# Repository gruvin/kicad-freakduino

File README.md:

# kicad-freakduino
## KiCADifying the Freakduino

I have longed for years to be able to make my own 2.4GHz, digital wireless radios.  Then I discovered and purchased a 
couple of <a href='http://www.freaklabsstore.com/index.php?main_page=product_info&cPath=22&products_id=204&zenid=f07iqog0jf6pku1qjimmd3q934'>FreakLabs "Freakduino v2.1a" boards</a>, 
as a means to learn more about low level, digital 2.4GHz RF communications. With my desire for learning, 
combined with my preference for open source EDA tools, this project was born.

<blockquote><i>Image right: Latest (final?) KiCAD-Freakduino prototype, version 1.2, revision r189</i></blockquote>

<blockquote><i>Building the three prototypes to get to this stage cost me enough to buy about ten original Freakduinos. 
Even to build one of my final version 1.2 boards, by hand and using retail priced parts, it costs significantly more 
than an original Freakduino. So if you just want to get up and running painlessly with a working board, I recommend 
you  simply <a href='http://www.freaklabsstore.com/index.php?main_page=product_info&cPath=22&products_id=204&zenid=f07iqog0jf6pku1qjimmd3q934'>buy the real thing</a>.</i></blockquote>

These Arduino compatible boards use an Atmel radio chip, intended for Zigbee standard communications. Akiba (of Freaklabs) 
wrote, "Chibi" (Japanese for "Midget") -- a light-weight communications stack, which works very well and makes 
understanding how things fit together in these systems very much simpler than a full ZigBee stack. Certainly, 
Chibi more than suffices for anything I can imagine needing for my own projects. The Arduino targeted version 
has its own project site named, <a href='http://www.freaklabs.org/index.php/chibiArduino.html'>chibiArduino</a>.

Eventually, I want to make my own boards, based on what I've learned here -- not Arduino boards, just MCU+RF 
chip and thus much smaller. In the meantime, since I had only theoretical experience with 2.4GHz radio 
communications, making my own version of a Freakduino board seemed like a good place to start. "Standing on 
the shoulders of giants", sort of thing. ;-)

I use only open source EDA tools (mostly KiCAD) for schematic capture and PCB layout design of my open source 
projects. This meant re-designing a schematic and board layout from scratch, based on the open materials 
published by FreakLabs, to whom we are all obviously very thankful. In the end, I also made a few minor 
changes to the design -- mostly due to different parts availability in my part of the world. But I've kept 
the overall layout very similar, so that the original Freakduino user-level documentation still applies 
-- jumper locations, switch settings, etc. For example, my version has a different 5-to-3.3 Volt  level 
shifter chip. The battery boost-regulator circuit is also different and is implemented in surface mount 
parts as a standard feature of the board.

The original Freakduino is already publicly licensed (Creative Commons Attribution-ShareAlike v3.0). But I 
wanted to let Akiba know what I was doing and to thank him personally for his work. I received his blessing 
2013-07-16 and immediately created this Google Code project. Thanks Akiba. I am sure we all really appreciate 
your efforts!

<h2>Progress as at 2013-11-07</h2>

My KiCAD design has now gone through several revisions and improvements. There are some changes to the 
components used, due to local availability as much as anything. But I've kept all the switches and jumper 
locations and functions the same as the original, such that the existing Freakduino v2.1a user documentation 
still applies.

I had revision <a href='https://code.google.com/p/kicad-freakduino/source/detail?r=101'>r101</a> PCBs 
fabricated. But there were errors found before those even arrived. Revision r116 was then fabricated 
and subsequently built. Unfortunately, that had errors as well and needed patching to get working. See 
<a href='Milestones.md'>Milestones</a> for details.

Finally, a version 1.2 revision r189 was built and seems to have come out all OK. Yay \o/

Below is a KiCAD 3D view of the present, r181 design, which is almost identical to the final 
r189 ...

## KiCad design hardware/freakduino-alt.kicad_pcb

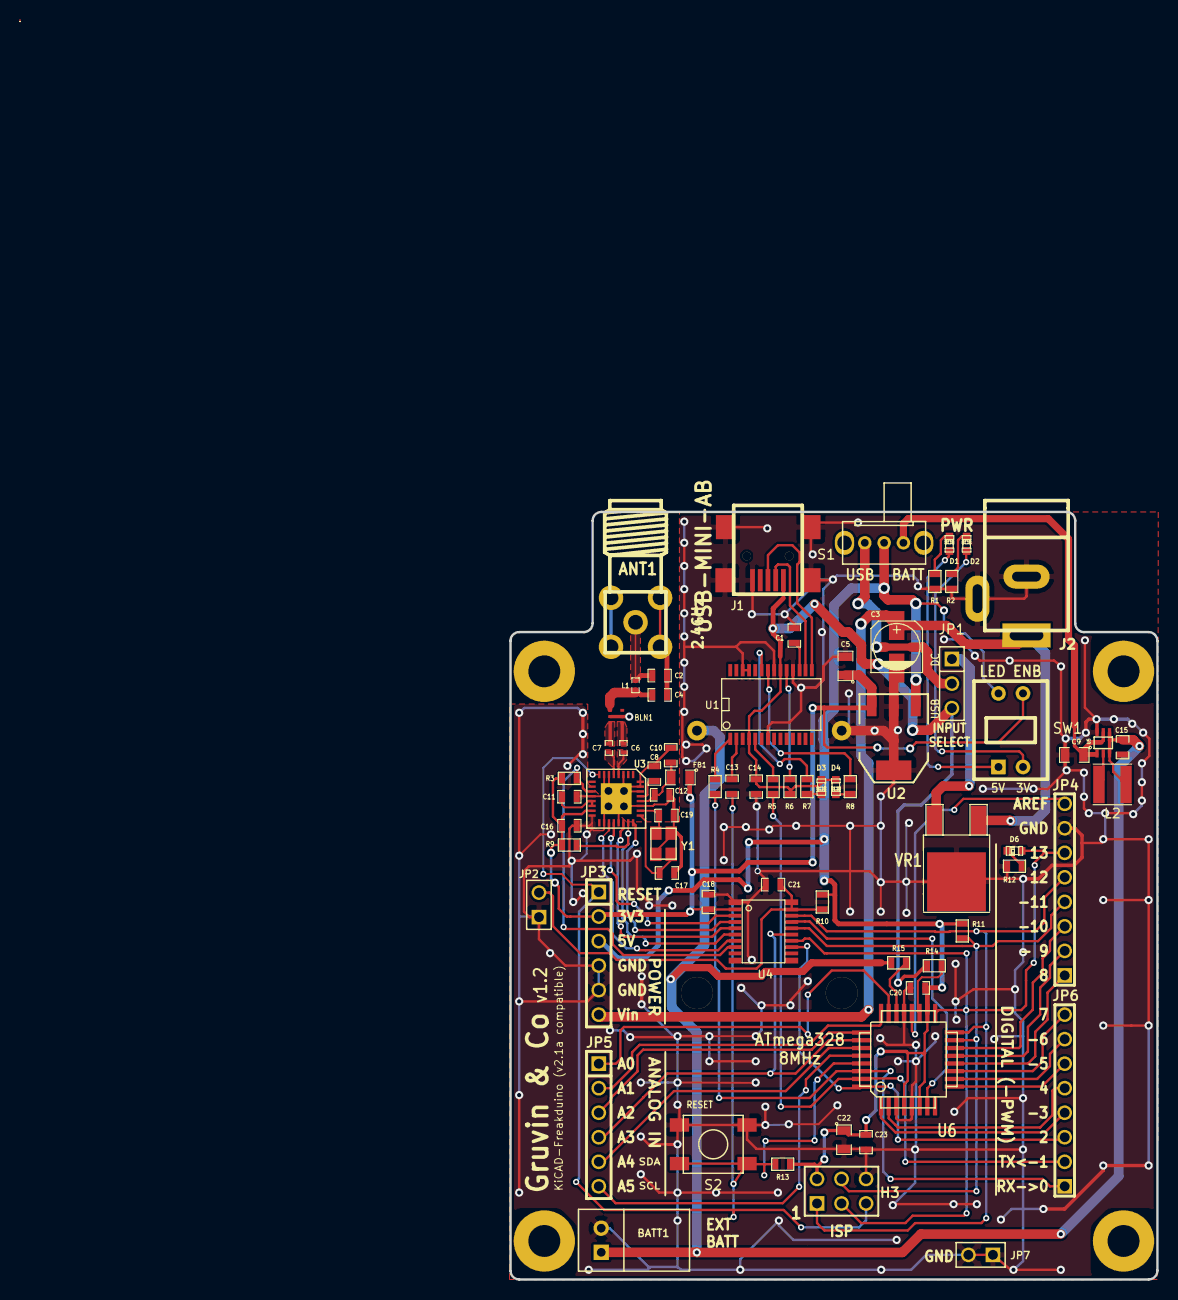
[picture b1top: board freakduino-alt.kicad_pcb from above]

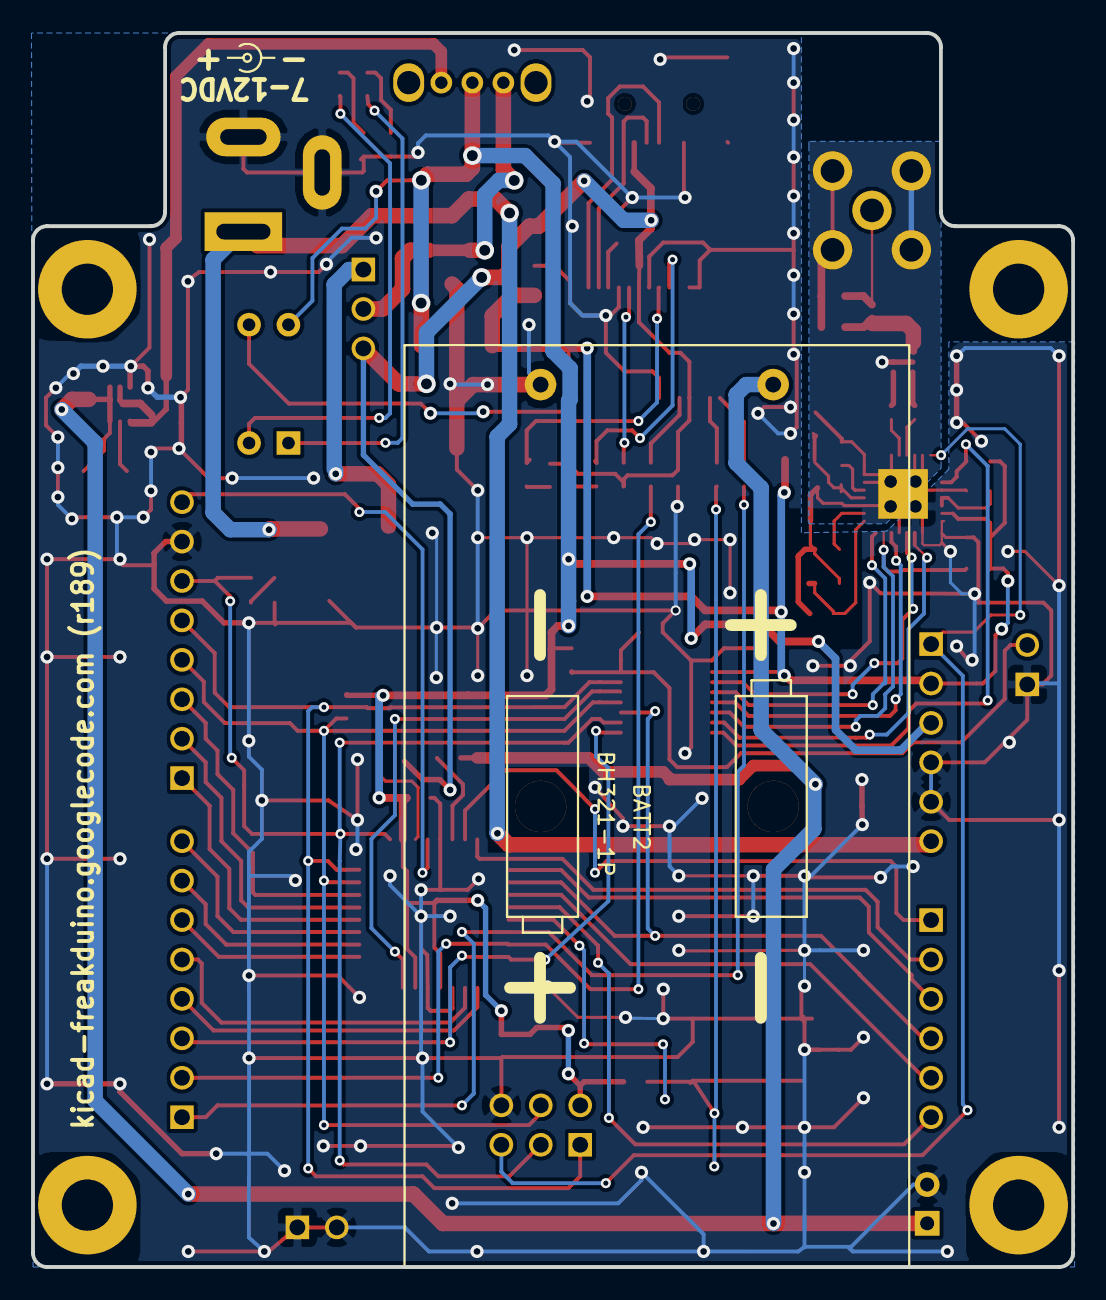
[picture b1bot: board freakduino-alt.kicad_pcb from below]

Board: 2 copper layers, 67.0 x 79.5 mm, 77 parts (2 on the bottom side), 69 nets.

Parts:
ANT1: SMA; SMA-GRUVIN
BATT1: BH321-1P; JST_S2B-XH-A
BATT2: BH321-1P; BATT_HOLDER_2AA
BLN1: 2450BL15B100E; BALUN_SMD_0805
C1, C10, C11, C13, C14, C16, C18, C20, C21, C23: 0u1; SM0603_Capa
C2: DNI; SM0603_Capa
C3: 100u/16V; c_elec_5x5.8
C4: 0p4; SM0603_Capa
C5: 22u/6V3; SM0805
C6, C7: 5p6; SM0402_c
C8, C12: 0u01; SM0603_Capa
C9: 22u/16V/TANT; SM0805
C15: 10u/10V; SM0603_Capa
C17, C19: 12p; SM0603_Capa
C22: 22u/6v3; SM0805
D1: BLUE; LED-0603
D2, D6: RED; LED-0603
D3, D4: GREEN; LED-0603
FB1: FB/0805; SM0805
H1, H2, H4, H5: MOUNT_HOLE; HOLE_130x250mil
H3: H3X2; pin_array_3x2
J1: USB-MINI-AB; USB-B_mini
J2: POWERJACK/THRU-3; JACK_NEB21R
JP1: JP3/THRU_VERT; PIN_ARRAY_3X1
JP2, JP7: 1X2; PIN_ARRAY_2X1
JP3, JP5: JP6/THRU; PIN_ARRAY-6X1
JP4, JP6: JP8/THRU; pin_array_8x1
L1: 3.3nH; SM0402
L2: 4.7uH; L_Taiyo-Yuden_NR-40xx
POWER_POLARITY_REF: VAL**; POWER_POLARITY_REF
R1, R2, R4, R5, R7, R8, R12: 1K; SM0603
R3, R9: DNI; SM0603
R6, R11, R13: 10K; SM0603
R10: 180K; SM0603
R14, R15: 100K; SM0603
S1: SW_SLIDE/THRU-3; SW_SPDT_SLIDE_90
S2: PBS_SMD; SWPUSH_SPST_SMD
STUB: VAL**; STUB
SW1: DIPSW4_DIP; SWDIP2
U1: FT232-SSOP28; SSOP28-GRUVIN
U2: TC1264; SOT223
U3: AT86RF231; QFN32_2x2-SINK
U4: GTL2003; SOT360-1
U5: TPS61222; SC-70-6
U6: ATMEGA328-QFP32; TQFP32
VR1: UA78M05CDCYG3; DPAK2
Y1: NX3225SA-16MHz-15ppm; crystal_C3E

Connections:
/INTERFACE/3VLED: D2.1, SW1.2
/INTERFACE/5VLED: D1.1, SW1.1
/INTERFACE/LOGIC_OE: C21.1, JP2.2, R10.1, U4.19, U4.20
/INTERFACE/VCC3_LED: D2.2, R2.2
/INTERFACE/VCC5_LED: D1.2, R1.2
/POWER/BOOST_OUT: C9.1, S1.1, U5.2, U5.4
/POWER/DC_IN: JP1.1, VR1.3
/POWER/VCC5_IN: JP1.2, S1.3
/RADIO/ANT: ANT1.1, C2.1, L1.2
/RADIO/RFN: C6.1, U3.4
/RADIO/RFN_BAL: BLN1.4, C6.2
/RADIO/RFP: C7.1, U3.5
/RADIO/RFP_BAL: BLN1.3, C7.2
/RADIO/UNBAL: BLN1.1, C4.1, L1.1
/USB/DM: J1.2, U1.16
/USB/DP: J1.3, U1.15
/USB/FTDI_RST_N: R6.2, U1.19
/USB/RXLED_N: R8.2, U1.22
/USB/TXLED_N: R7.2, U1.23
/USB/USB_3V3OUT: C1.1, U1.17
/VBATR: R15.2, U6.22
/VBUSR: R14.2, U6.19
AREF: JP4.8, U6.20
DTR_N: C13.1, U1.2
INT: U3.24, U4.4
MCU_RX: R4.2, U1.1
MCU_TX: R5.2, U1.5
MISO: U3.20, U4.3
MOSI: U3.22, U4.5
unnamed: L2.2, U5.5
unnamed: C8.1, U3.29
unnamed: C17.1, U3.25, Y1.3
unnamed: C19.1, U3.26, Y1.1
unnamed: C11.1, U3.13, U3.14
unnamed: C10.1, C12.1, FB1.2, U3.28
unnamed: D4.2, R8.1
unnamed: D3.2, R7.1
unnamed: D6.2, R12.2
PB0/ICP1: JP4.1, U6.12
PB1/OC1A: JP4.2, U6.13
PB2/~SS~/OC1B: JP4.3, U6.14
PB3/MOSI/OC2A: H3.4, JP4.4, R11.1, U4.16, U6.15
PB4/MISO: H3.1, JP4.5, U4.18, U6.16
PB5/SCLK: D6.1, H3.3, JP4.6, U4.14, U6.17
PC0/ADC0: JP5.1, U6.23
PC1/ADC1: JP5.2, U6.24
PC2/ADC2: JP5.3, U6.25
PC3/ADC3: JP5.4, U4.15, U6.26
PC4/ADC4/SDA: JP5.5, U6.27
PC5/ADC5/SCL: JP5.6, U6.28
PD0/RXD: JP6.1, R4.1, U6.30
PD1/TXD: JP6.2, R5.1, U6.31
PD2/INT0: JP6.3, U4.13, U6.32
PD3/INT1/OC2B: JP6.4, U6.1
PD4/T0: JP6.5, U6.2
PD5/T1/OC0B: JP6.6, U6.9
PD6/OC0A/AIN0: JP6.7, U6.10
PD7/AIN1: JP6.8, U6.11
RADIO_INT: U4.17, U6.7
RADIO_SEL_N: R9.2, U3.23, U4.6
RESET_N: C13.2, H3.5, JP3.1, R13.1, S2.3, S2.4, U3.8, U6.29
SCLK: U3.19, U4.7
SLP_TR: R3.2, U3.11, U4.8
VBAT: BATT1.1, BATT2.1, C15.1, L2.1, R15.1, U5.1, U5.6
VBUS: C14.1, D3.1, D4.1, J1.1, JP1.3, R6.1, R14.1, U1.4, U1.20
VCC3: C5.1, C16.1, C18.1, FB1.1, JP3.2, R3.1, R9.1, SW1.3, U2.3, U3.15, U4.2
VCC5: C20.1, C22.1, C23.1, H3.2, JP3.3, R10.2, R11.2, R13.2, S1.2, SW1.4, U2.1, U6.4, U6.6, U6.18
VCC_IN: C3.1, J2.1, JP3.6, VR1.1
VSS: ANT1.2, ANT1.3, ANT1.4, ANT1.5, BATT1.2, BATT2.2, BLN1.2, BLN1.5, C1.2, C2.2, C3.2, C4.2, C5.2, C8.2, C9.2, C10.2, C11.2, C12.2, C14.2, C15.2, C16.2, C17.2, C18.2, C19.2, C20.2, C21.2, C22.2, C23.2, H3.6, J1.5, J1.6, J1.7, J1.8, J1.9, J2.2, J2.3, JP2.1, JP3.4, JP3.5, JP4.7, JP7.1, JP7.2, R1.1, R2.1, R12.1, S2.1, S2.2, U1.7, U1.18, U1.21, U1.25, U1.26, U2.2, U2.4, U3.3, U3.6, U3.7, U3.12, U3.16, U3.18, U3.21, U3.27, U3.30, U3.31, U3.32, U3.33, U4.1, U5.3, U6.3, U6.5, U6.21, VR1.2, Y1.2, Y1.4

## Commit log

2015-06-03 Added images from old Google Code wiki
2015-06-03 Add two old Google Code wiki pages
2018-08-28 Laboriously re-worked schematic and 3D settings for KiCAD v5+
2018-08-28 Attempting to update sch->brd netlist component footprint a for KiCAD v5+
